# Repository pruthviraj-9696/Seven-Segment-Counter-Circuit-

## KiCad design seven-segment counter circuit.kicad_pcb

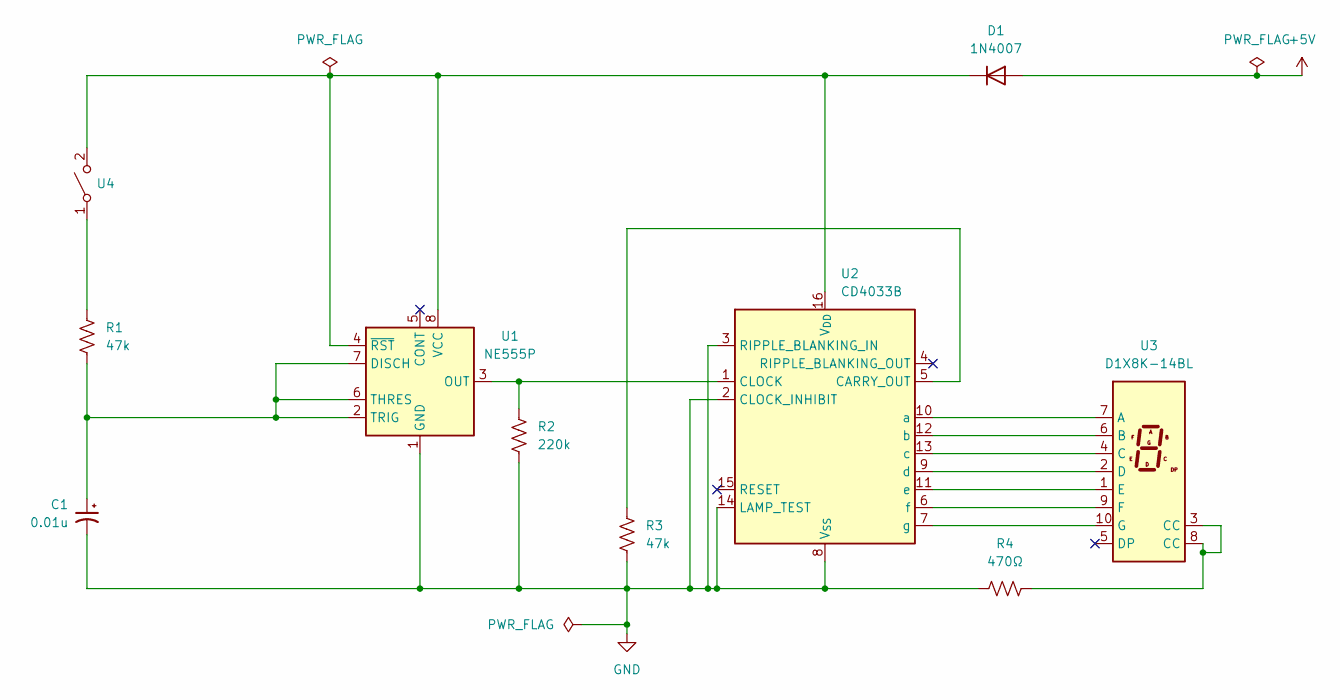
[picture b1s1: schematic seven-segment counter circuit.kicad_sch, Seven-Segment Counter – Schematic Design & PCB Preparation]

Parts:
C1: 0.01u; C_Disc_D5.0mm_W2.5mm_P5.00mm
D1: 1N4007; D_DO-41_SOD81_P10.16mm_Horizontal
R1, R3: 47k; R_Axial_DIN0207_L6.3mm_D2.5mm_P2.54mm_Vertical
R2: 220k; R_Axial_DIN0207_L6.3mm_D2.5mm_P2.54mm_Vertical
R4: 470Ω; R_Axial_DIN0207_L6.3mm_D2.5mm_P2.54mm_Vertical
U1: NE555P; DIP-8_W7.62mm
U2: CD4033B; DIP-16_W7.62mm
U3: D1X8K-14BL; D1X8K
U4: SW_DIP_SPSTx01_Slide_6.7x4.1mm_W8.61mm_P2.54mm_LowProfile

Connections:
+5V: D1.2 (A)
GND: C1.2, R2.2, R3.2, R4.1, U1.1 (GND), U2.2 (CLOCK_INHIBIT), U2.3 (RIPPLE_BLANKING_IN), U2.8 (V_{SS}), U2.14 (LAMP_TEST)
unnamed: D1.1 (K), U1.4 (~RST), U1.8 (VCC), U2.16 (V_{DD}), U4.2 (B)
unnamed: R4.2, U3.3 (CC), U3.8 (CC)
unnamed: C1.1, R1.2, U1.2 (TRIG), U1.6 (THRES), U1.7 (DISCH)
unnamed: R2.1, U1.3 (OUT), U2.1 (CLOCK)
unnamed: R3.1, U2.5 (CARRY_OUT)
unnamed: U2.10 (a), U3.7 (A)
unnamed: U2.12 (b), U3.6 (B)
unnamed: U2.13 (c), U3.4 (C)
unnamed: U2.9 (d), U3.2 (D)
unnamed: U2.11 (e), U3.1 (E)
unnamed: U2.6 (f), U3.9 (F)
unnamed: U2.7 (g), U3.10 (G)
unnamed: R1.1, U4.1 (A)

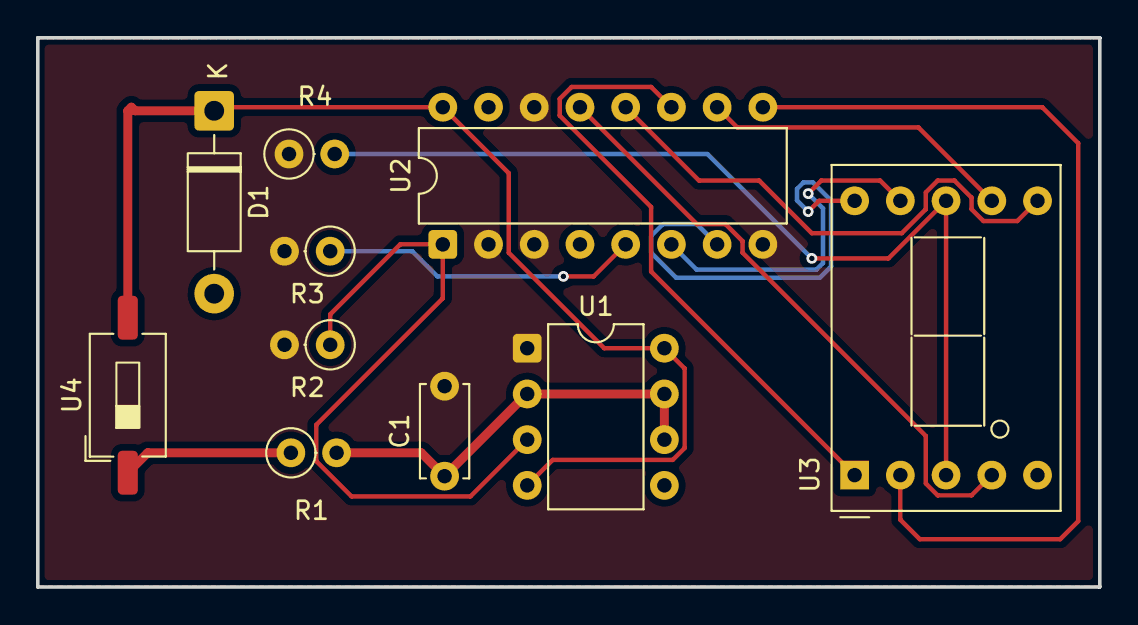
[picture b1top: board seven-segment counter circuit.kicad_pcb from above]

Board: 2 copper layers, 59.0 x 30.5 mm, 10 parts (0 on the bottom side), 14 nets.
